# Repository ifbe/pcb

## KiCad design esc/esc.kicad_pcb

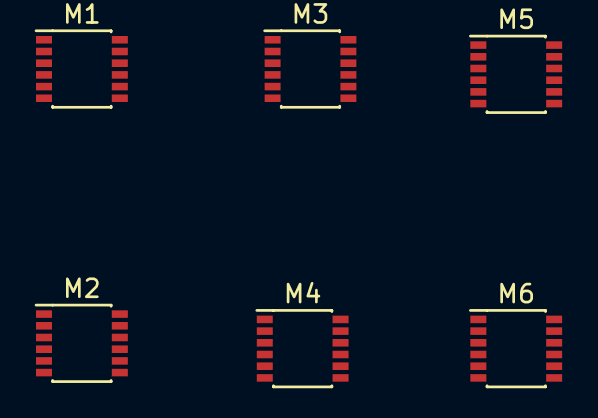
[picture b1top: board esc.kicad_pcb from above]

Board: 2 copper layers, 6 parts (0 on the bottom side), 5 nets, no tracks yet.

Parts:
M1, M2, M3, M4, M5, M6: MNMOS; MSOP-12_3x4mm_P0.65mm

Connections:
GND: M2.3, M4.3, M6.3
unnamed: M1.3, M1.4, M2.1
unnamed: M3.3, M3.4, M4.1
unnamed: M5.3, M5.4, M6.1
VCC: M1.1, M3.1, M5.1

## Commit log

2018-11-02 electronic speed controller?
2018-12-12 dirs
2019-02-01 buckboost
